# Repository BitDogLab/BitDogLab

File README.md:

<h1 align="center">BitDogLab V7</h1>

<p align="center">
  Open-source educational hardware for embedded systems, programming, electronics, and physical computing.
</p>

<p align="center">
  <a href="README.md">English</a> |
  <a href="README.pt-BR.md">Português</a>
</p>

<p align="center">
  
  <br>
  <a href="https://comunidade-bitdoglab.web.app">https://comunidade-bitdoglab.web.app</a>
</p>

<p align="center">
  Não é da área de tecnologia? Este repositório é o espaço técnico do projeto — para professores e demais usuários, a <a href="https://comunidade-bitdoglab.web.app"><strong>Comunidade BitDogLab</strong></a> é uma porta de entrada mais amigável, com documentação, códigos e aplicações prontas.
</p>

BitDogLab is an initiative of the **Escola 4.0 project at FEEC/Unicamp**. It brings together the Raspberry Pi Pico ecosystem and the main peripherals used in embedded systems, providing a practical platform for education, experimentation, and project development.

The current board is **BitDogLab Version 7**, with support for Raspberry Pi Pico-compatible modules based on the **RP2040** and **RP2350** microcontrollers.

Its hands-on approach supports the development of scientific thinking, problem solving, collaboration, and digital culture, competencies emphasized by Brazil's National Common Curricular Base (BNCC).

---

## Board and Peripherals

The board provides direct access to the main resources used in embedded-system education, including buttons, joystick, RGB LED, LED matrix, OLED display, microphone, buzzer, sensors, and expansion connectors.

---

## Recommended Learning Path

```mermaid
flowchart LR
    A[Start Here guide] --> B[Basic MicroPython examples]
    B --> C[Peripheral guides and libraries]
    C --> D[Applications and projects]
    D --> E[Hardware design and fabrication]
```

1. Follow the [Start Here guide](COMECE_POR_AQUI_BitDogLab_V7_MicroPython.md) to prepare the board and run the first test.
2. Study the [`basic-examples/`](basic-examples/) directory, organized from simpler to more advanced peripherals.
3. Use the [V7 peripheral guides](doc/Bitdoglab%20V7/) and reusable [`libs_software/`](libs_software/) modules.
4. Explore and develop applications in [`projects/`](projects/).
5. Study or manufacture the board using the public files in [`pcb-prototyping/`](pcb-prototyping/).

---

## Start Programming

The fastest text-based path is MicroPython with Thonny:

- [Illustrated MicroPython start guide](COMECE_POR_AQUI_BitDogLab_V7_MicroPython.md)
- [60 basic peripheral examples](basic-examples/README.md)
- [Complete peripheral test](testar_perifericos_gerais.py)
- [MicroPython firmware](firmware/)
- [Reusable software libraries](libs_software/README.md)

---

## Active Programming Projects

Below are the tools currently being developed within the BitDogLab ecosystem to support different entry points into programming — from block-based logic to AI-assisted code generation.

### 🧩 Blockly for BitDogLab

Blockly is the easiest way to get started with BitDogLab. It is designed for students and beginners learning programming logic and embedded systems. The tool runs directly in the browser without requiring installation.

To use it:

[Open Blockly for BitDogLab](https://bitdoglab-blocos.github.io/BIPES-BITDOGLAB/ui/)

1. Connect the BitDogLab to the computer using a USB cable.
2. Open Blockly for BitDogLab, preferably in Chrome or Edge.
3. Select the serial port corresponding to the board.
4. Drag and connect blocks to create the program.
5. Click `Run` or `Upload` to send the program to the BitDogLab.

> **Important:** If the board already contains a file named `main.py`, remove it before using Blockly. This file can prevent the tool from communicating correctly with the microcontroller.

<br>

### 📄 BIH — Hardware Information Database

<p align="center">
  
</p>

The **BIH** is a hardware information database designed to adapt the BitDogLab technical context for Large Language Models (LLMs), including ChatGPT, Gemini, and other AI assistants.

It describes the board's pin assignments, peripherals, interfaces, and hardware constraints. By providing the BIH to an LLM before requesting a program, the model can generate MicroPython or C/C++ code that better matches the BitDogLab hardware.

- [Open the BitDogLab V7 BIH](https://docs.google.com/document/d/13-68OqiU7ISE8U2KPRUXT2ISeBl3WPhXjGDFH52eWlU/edit?usp=sharing)
- [Open the visual hardware database](https://docs.google.com/document/d/1-2Eoo6H1gfTAlxZgFs26p7X4CeaLkS8X8hNTC96PetQ/edit?usp=sharing)

<br>

### 🔀 FluxCode

O BitDogLab FluxCode é um aplicativo Android que usa **IA multimodal** para transformar fluxogramas desenhados à mão em código **MicroPython** pronto para rodar na BitDogLab. A proposta é desplugada: o estudante primeiro desenvolve a lógica no papel usando símbolos de fluxograma, fotografa o desenho pelo app e recebe automaticamente o código correspondente, que pode ser executado ou salvo direto na placa.

Para usar:

[Baixar o BitDogLab FluxCode](https://drive.google.com/drive/folders/12xD7rVUsgQWKkneTLb5EA2QpiOx43nXb?usp=drive_link)

1. Conecte a BitDogLab ao smartphone via USB.
2. Desenhe o fluxograma em papel usando o gabarito de símbolos.
3. No app, toque em **Foto Código** e fotografe o fluxograma.
4. Revise o código MicroPython e o pseudocódigo gerados automaticamente.
5. Toque em **Executar** para rodar na placa, ou salve como `main.py` para execução automática ao ligar.

> Disponível apenas para Android. Requer MicroPython instalado na placa e um cabo USB compatível com transferência de dados (não apenas carregamento).

<br>

### 🎨 Pixel Art Application

**UNDER CONSTRUCTION**

---

## BitDogLab V7 Hardware

BitDogLab V7 integrates an RGB LED, a 5x5 WS2812B matrix, three buttons, analog joystick, buzzer, analog microphone, OLED display, power monitoring, and expansion connections around a Raspberry Pi Pico-compatible module.

The V7 hardware was developed in **Altium Designer**. Source files, schematic, PCB layout, BOM, pick-and-place data, STEP model, and public Gerber files for fabrication are available in [`pcb-prototyping/BitDogLab V7/`](pcb-prototyping/BitDogLab%20V7/).

BitDogLab V6 was developed in **KiCad** and remains available for study and fabrication. See the complete [PCB and fabrication documentation](pcb-prototyping/README.md).

---

## Repository Structure

| Path | Content |
|---|---|
| [`basic-examples/`](basic-examples/) | Beginner-friendly MicroPython examples organized by peripheral. |
| [`doc/`](doc/) | BitDogLab V6 and V7 documentation and peripheral guides. |
| [`firmware/`](firmware/) | MicroPython firmware and installation resources. |
| [`libs_software/`](libs_software/) | Reusable MicroPython drivers and helper modules. |
| [`pcb-prototyping/`](pcb-prototyping/) | PCB source files and public manufacturing files. |
| [`projects/`](projects/) | Applications, sensors, IoT, tools, and hardware expansions. |

---

## Open Hardware and License

BitDogLab is open hardware. Its design and fabrication files are publicly available for study, modification, and manufacturing.

The project is licensed under the **CERN Open Hardware Licence Version 2 - Strongly Reciprocal (CERN-OHL-S v2.0)**. See [`LICENSE`](LICENSE).

---

## Initiative and Contributors

- Initiative: **Escola 4.0 - FEEC/Unicamp**
- Project coordination: **Prof. Dr. Fabiano Fruett**
- Contributors: students and collaborators from Escola 4.0 and FEEC/Unicamp
- Support: IEEE-EDS STEM outreach program and CNPq - INCT Namitec

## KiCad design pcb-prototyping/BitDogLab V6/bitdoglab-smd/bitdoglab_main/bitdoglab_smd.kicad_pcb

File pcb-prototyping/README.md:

# PCB Prototyping / Prototipagem de PCB

[English](#english) | [Portugues](#portugues)

## English

This directory contains the public PCB design and fabrication files for the BitDogLab boards.

The folder name is `pcb-prototyping` because not every file here was created in KiCad. It includes KiCad projects, Altium projects, manufacturing outputs, 3D models, images, BOM files and support libraries.

### Folder Structure

```text
pcb-prototyping/
+-- BitDogLab V6/
|   +-- bitdoglab-through-hole/
|   +-- bitdoglab-smd/
|   +-- component-libraries/
+-- BitDogLab V7/
    +-- Project Outputs for BitDogLab V7/
    +-- __Previews/
    +-- History/
    +-- bitdoglab-v7-pcb-top-view.png
    +-- bitdoglab-v7-pcb-bottom-view.png
```

### BitDogLab V6

BitDogLab V6 was developed in KiCad.

- `bitdoglab-through-hole/`: through-hole/DIY KiCad project files.
- `bitdoglab-smd/`: SMD KiCad project files, schematic, PCB layout, fabrication outputs and board images.
- `component-libraries/`: symbols, footprints, 3D models and support files used by the KiCad projects.

Common KiCad files found here:

- `.kicad_pro`: KiCad project file.
- `.kicad_sch`: schematic file.
- `.kicad_pcb`: PCB layout file.
- `.kicad_mod`: footprint file.
- `.kicad_sym`: symbol library file.
- `.step` / `.stp`: 3D model files.
- `.zip`: fabrication package when available.
- `.csv` / `.xlsx`: BOM or component data when available.

### BitDogLab V7

BitDogLab V7 was developed in Altium Designer.

Main files:

- `BitDogLab V7.PrjPcb`: Altium PCB project.
- `BitDogLab V7.SchDoc`: Altium schematic document.
- `BitDogLab V7.PcbDoc`: Altium PCB layout document.
- `BitDogLab V7.OutJob`: Altium output job configuration.
- `BitDogLab V7.pdf`: exported schematic/documentation PDF.
- `BitDogLab V7_Lista de Materiais com Custo.xlsx`: bill of materials with cost information.
- `BitDogLab V7_Gerber.rar`: Gerber fabrication package.
- `Project Outputs for BitDogLab V7/`: manufacturing outputs exported from the project, including Gerber layers, drill reports, BOM, pick-and-place and 3D STEP model.
- `bitdoglab-v7-pcb-top-view.png`: technical top view image of the PCB.
- `bitdoglab-v7-pcb-bottom-view.png`: technical bottom view image of the PCB.

### Public Fabrication Files

Gerber files are publicly available for fabrication. They can be used by PCB manufacturers to produce the board.

Before ordering a board, review the fabrication package, BOM, drill files and pick-and-place data. Manufacturing settings can vary by supplier, so the files should always be checked in a Gerber viewer or CAM tool before production.

### Notes

- KiCad is recommended for opening and editing the BitDogLab V6 project files.
- Altium Designer is recommended for opening and editing the BitDogLab V7 source project files.
- Gerber and drill files can usually be inspected with vendor tools or independent Gerber viewers.
- Board images are provided as visual references and are not a replacement for fabrication data.

## Portugues

Esta pasta contem os arquivos publicos de projeto e fabricacao das placas BitDogLab.

O nome da pasta e `pcb-prototyping` porque nem todo arquivo aqui foi desenvolvido no KiCad. Ela inclui projetos KiCad, projetos Altium, arquivos de fabricacao, modelos 3D, imagens, listas de materiais e bibliotecas de apoio.

### Estrutura de Pastas

```text
pcb-prototyping/
+-- BitDogLab V6/
|   +-- bitdoglab-through-hole/
|   +-- bitdoglab-smd/
|   +-- component-libraries/
+-- BitDogLab V7/
    +-- Project Outputs for BitDogLab V7/
    +-- __Previews/
    +-- History/
    +-- bitdoglab-v7-pcb-top-view.png
    +-- bitdoglab-v7-pcb-bottom-view.png
```

### BitDogLab V6

A BitDogLab V6 foi desenvolvida no KiCad.

- `bitdoglab-through-hole/`: arquivos KiCad da versao through-hole/DIY.
- `bitdoglab-smd/`: arquivos KiCad da versao SMD, esquematico, layout da placa, saidas de fabricacao e imagens da placa.
- `component-libraries/`: simbolos, footprints, modelos 3D e arquivos de apoio usados pelos projetos KiCad.

Arquivos KiCad comuns nesta pasta:

- `.kicad_pro`: arquivo de projeto KiCad.
- `.kicad_sch`: arquivo de esquematico.
- `.kicad_pcb`: arquivo de layout da PCB.
- `.kicad_mod`: arquivo de footprint.
- `.kicad_sym`: biblioteca de simbolos.
- `.step` / `.stp`: modelos 3D.
- `.zip`: pacote de fabricacao quando disponivel.
- `.csv` / `.xlsx`: BOM ou dados de componentes quando disponiveis.

### BitDogLab V7

A BitDogLab V7 foi desenvolvida no Altium Designer.

Arquivos principais:

- `BitDogLab V7.PrjPcb`: projeto PCB do Altium.
- `BitDogLab V7.SchDoc`: documento de esquematico do Altium.
- `BitDogLab V7.PcbDoc`: documento de layout da PCB no Altium.
- `BitDogLab V7.OutJob`: configuracao de saidas do Altium.
- `BitDogLab V7.pdf`: PDF exportado com esquematico/documentacao.
- `BitDogLab V7_Lista de Materiais com Custo.xlsx`: lista de materiais com informacoes de custo.
- `BitDogLab V7_Gerber.rar`: pacote Gerber para fabricacao.
- `Project Outputs for BitDogLab V7/`: saidas de fabricacao exportadas do projeto, incluindo camadas Gerber, relatorios de furo, BOM, pick-and-place e modelo 3D STEP.
- `bitdoglab-v7-pcb-top-view.png`: imagem tecnica da face superior da PCB.
- `bitdoglab-v7-pcb-bottom-view.png`: imagem tecnica da face inferior da PCB.

### Arquivos Publicos para Fabricacao

Os arquivos Gerber estao disponiveis publicamente para fabricacao. Eles podem ser usados por fabricantes de PCB para produzir a placa.

Antes de encomendar uma placa, revise o pacote de fabricacao, a BOM, os arquivos de furo e os dados de pick-and-place. As configuracoes de fabricacao podem variar conforme o fornecedor, entao os arquivos devem sempre ser conferidos em um visualizador Gerber ou ferramenta CAM antes da producao.

### Observacoes

- O KiCad e recomendado para abrir e editar os arquivos da BitDogLab V6.
- O Altium Designer e recomendado para abrir e editar os arquivos fonte da BitDogLab V7.
- Arquivos Gerber e de furo normalmente podem ser inspecionados em ferramentas dos fabricantes ou em visualizadores Gerber independentes.
- As imagens da placa servem como referencia visual e nao substituem os arquivos de fabricacao.

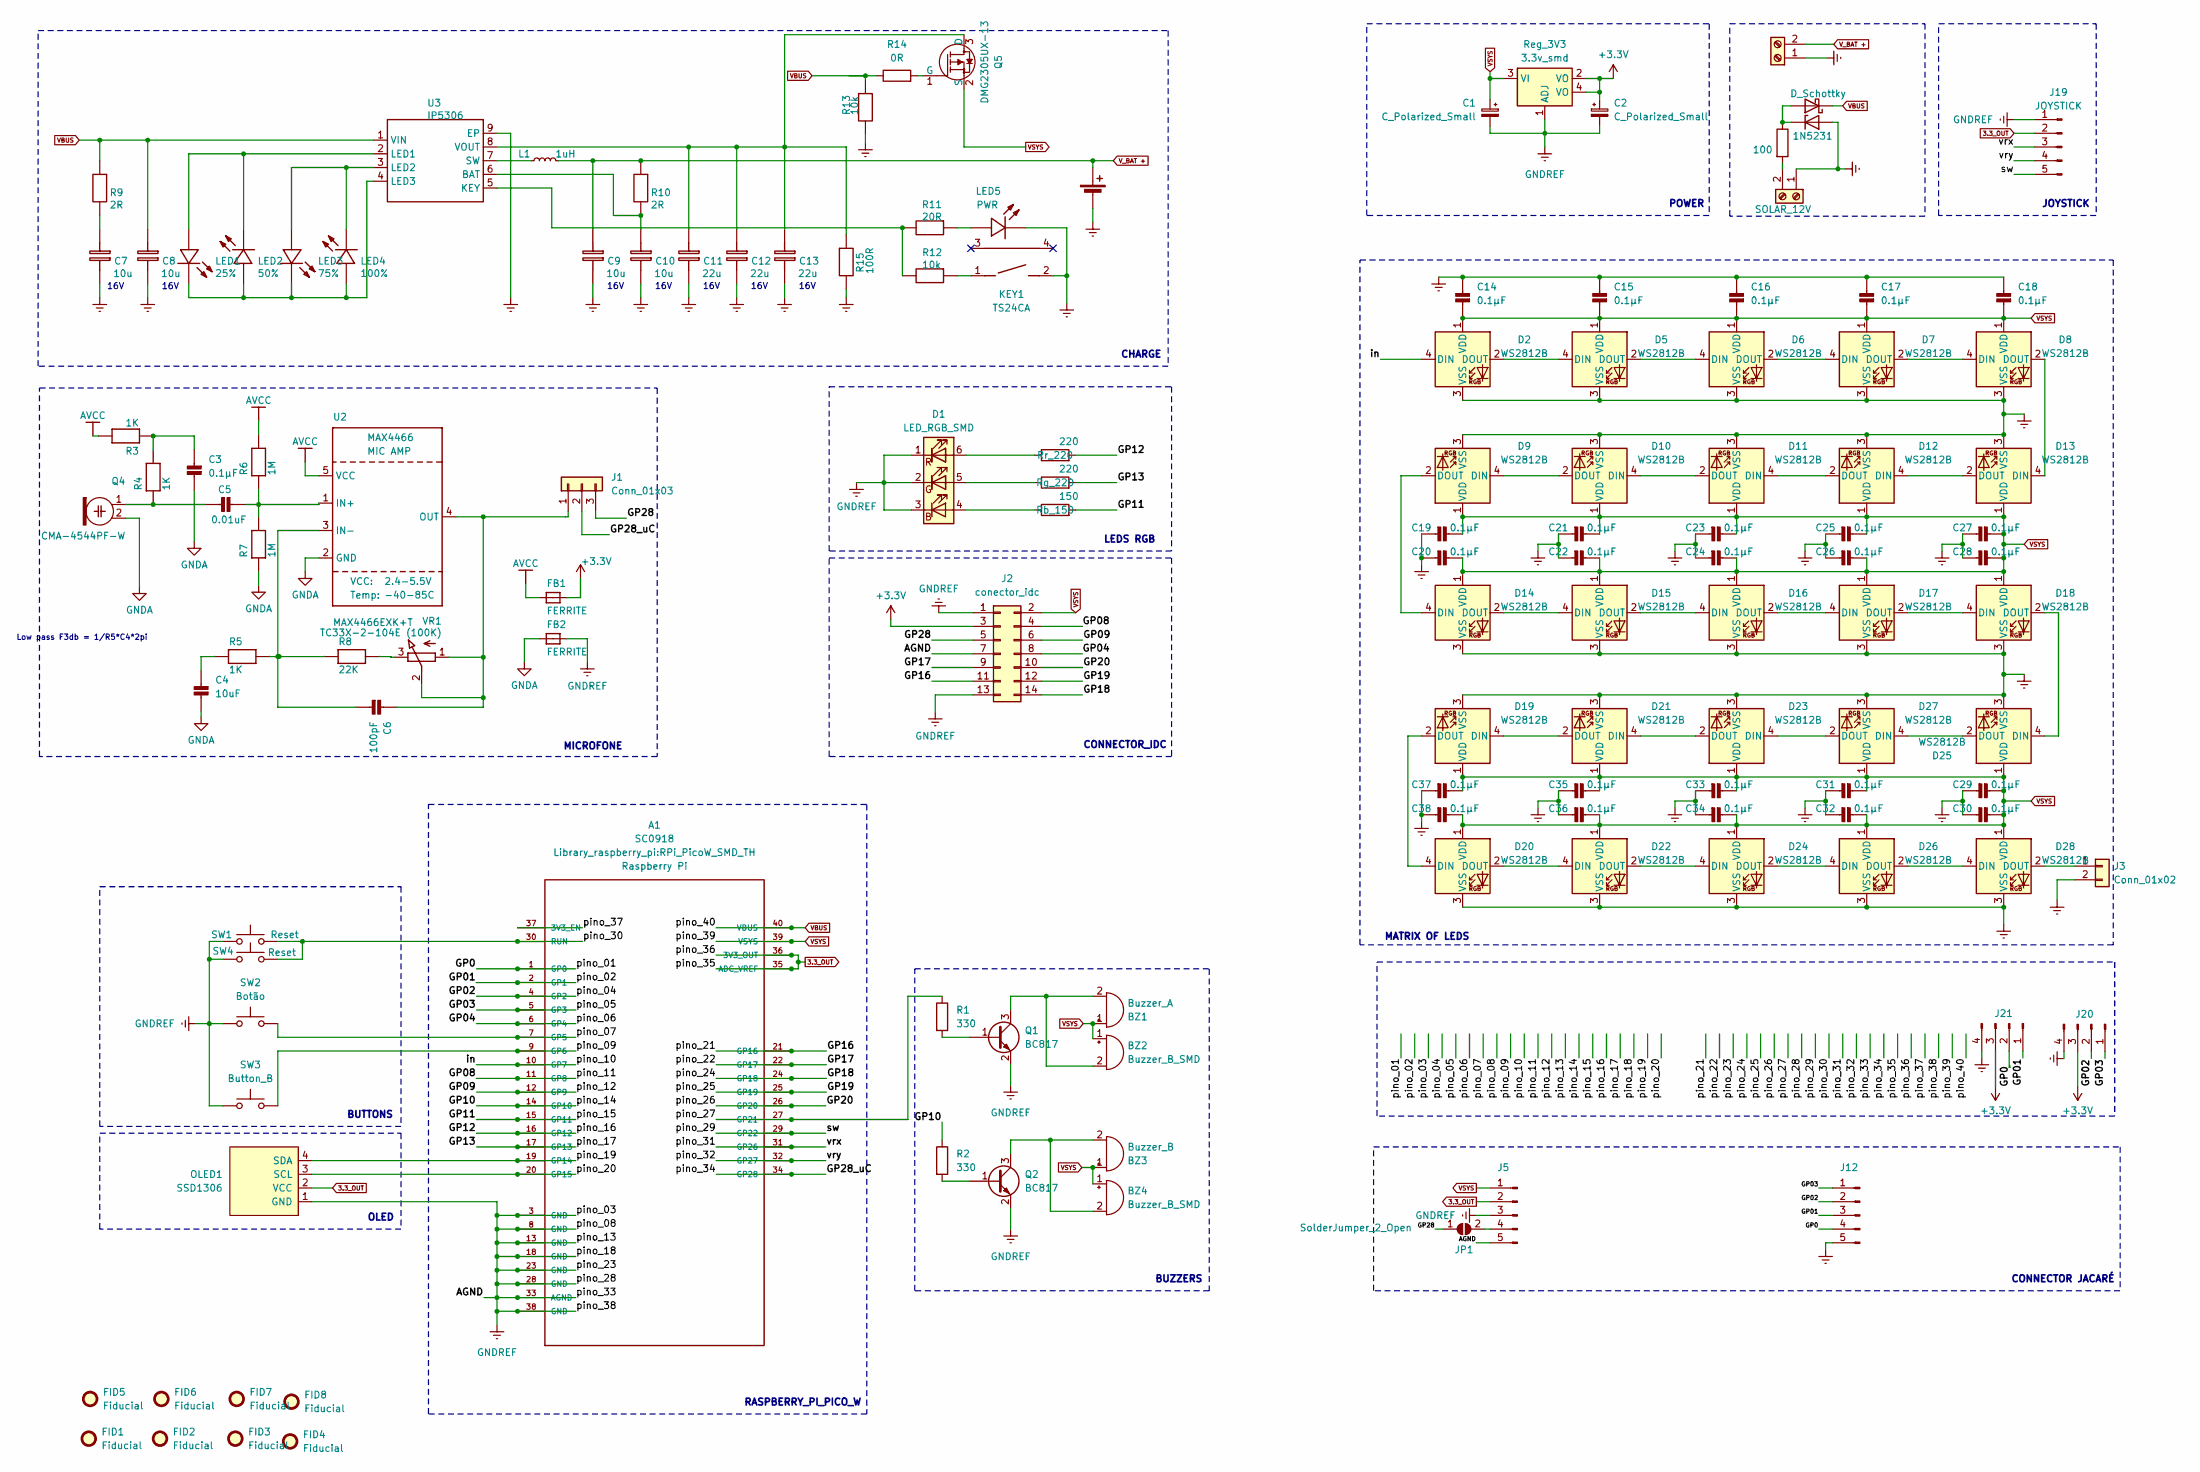
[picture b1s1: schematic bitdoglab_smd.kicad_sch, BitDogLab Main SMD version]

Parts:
A1: SC0918; RPi_PicoW_SMD_TH; PARTREV 1.6
BT1: Battery_Cell; BatteryHolder_MPD_BH-18650-PC2
BZ1: Buzzer_A; Buzzer_12x9.5RM7.6
BZ2, BZ4: Buzzer_B_SMD; MagneticBuzzer_CUI_CMT-8504-100-SMT
BZ3: Buzzer_B; Buzzer_12x9.5RM7.6
C1, C2: C_Polarized_Small; CP_Elec_5x5.9
C3, C14, C15, C16, C17, C18, C19, C20, C21, C22, C23, C24, C25, C26, C27, C28, C29, C30, C31, C32, C33, C34, C35, C36, C37, C38: 0.1µF; C_0402_1005Metric
C4: 10uF; C_0805_2012Metric
C5: 0.01uF; C_0402_1005Metric
C6: 100pF; C_0402_1005Metric
C7, C8, C9, C10: 10u; R_0805_2012Metric; MANUFACTURER PART CL21A106KAYNNNE
C11, C12, C13: 22u; R_0805_2012Metric; MANUFACTURER PART CL21A226MAQNNNE
CARGA_SOLAR1: SOLAR_12V; JST_EH_B2B-EH-A_1x02_P2.50mm_Vertical
D1: LED_RGB_SMD; LED_RGB_5050-6
D2, D5, D6, D7, D8, D9, D10, D11, D12, D13, D14, D15, D16, D17, D18, D19, D20, D21, D22, D23, D24, D25, D26, D27, D28: WS2812B; LED_WS2812B_PLCC4_5.0x5.0mm_P3.2mm
D3: 1N5231; D_T-1_P5.08mm_Horizontal
D4: D_Schottky; D_SOD-123
FB1, FB2: FERRITE; L_0603_1608Metric
FID1, FID2, FID3, FID4, FID5, FID6, FID7, FID8: Fiducial; Fiducial_1mm_Mask2mm
J1: Conn_01x03; PinHeader_1x03_P2.54mm_Vertical
J2: conector_idc; PinHeader_2x07_P2.54mm_Vertical
J3: Conn_01x02; PinHeader_1x02_P2.54mm_Vertical
J5, J12: Conn_01x05_Pin; PinHeader_1x05_P2.54mm_Vertical
J19: JOYSTICK; ky-023
J20, J21: Conn_01x04_Pin; JST_EH_B4B-EH-A_1x04_P2.50mm_Vertical
JP1: SolderJumper_2_Open; SolderJumper-2_P1.3mm_Open_TrianglePad1.0x1.5mm
KEY1: TS24CA; SW_SPST_CK_KMS2xxGP; MANUFACTURER PART TS24CA
L1: 1uH; L_Bourns_SRP7028A_7.3x6.6mm
LED1: 25%; LED_0805_2012Metric; MANUFACTURER PART FC-2012HRK-620D
LED2: 50%; LED_0805_2012Metric; MANUFACTURER PART 17-21SUYC/TR8
LED3: 75%; LED_0805_2012Metric; MANUFACTURER PART 17-21SUYC/TR8
LED4: 100%; LED_0805_2012Metric; MANUFACTURER PART 0805G (Green)
LED5: PWR; LED_0805_2012Metric; MANUFACTURER PART ORH-B35A
OLED1: SSD1306; 128x64OLED
Q1, Q2: BC817; SOT-23
Q4: CMA-4544PF-W; Buzzer_12x9.5RM7.6
Q5: DMG2305UX-13; SOT-23-3; MPN DMG2305UX-13; Digi-Key_PN DMG2305UX-13DICT-ND
R1, R2: 330; R_0603_1608Metric
R3, R4, R5: 1K; R_0603_1608Metric
R6, R7: 1M; R_0603_1608Metric
R8: 22K; R_0603_1608Metric
R9, R10: 2R; R_0603_1608Metric; MANUFACTURER PART RS-05L2R00FT
R11: 20R; R_0603_1608Metric; MANUFACTURER PART 0805W8F200JT5E
R12, R13: 10k; R_0603_1608Metric; MANUFACTURER PART 0805W8F1002T5E
R14: 0R; R_0603_1608Metric
R15: 100R; R_1210_3225Metric; MANUFACTURER PART RC1210FR-07100RL
R_1W1: 100; R_0603_1608Metric
Rb_150: 150; R_0603_1608Metric
Reg_3V3: 3.3v_smd; SOT-223
Rg_220: 220; R_0603_1608Metric
Rr_220: 220; R_0603_1608Metric
SW1: Reset; SW_PUSH_6mm
SW2: Botão; SW_PUSH_6mm_b
SW3: Button_B; SW_PUSH_6mm_b
SW4: Reset; SW_Push_1P1T_NO_6x6mm_H9.5mm
U2: MAX4466EXK+T; SOT-353_SC-70-5
U3: IP5306; SOP-8_5.28x5.23mm_P1.27mm; MANUFACTURER PART IP5306_4.35V
VR1: TC33X-2-104E (100K); Potentiometer_Bourns_TC33X_Vertical
V_BAT1: V_BAT; JST_EH_B2B-EH-A_1x02_P2.50mm_Vertical

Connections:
3.3_OUT: A1.35 (ADC_VREF), A1.36 (3V3_OUT), J5.2, J19.2, OLED1.2 (VCC)
+3.3V: C2.1, FB1.2, J2.3, J20.3, J21.3, Reg_3V3.2 (VO), Reg_3V3.4 (VO)
/GP0: A1.1 (GP0), J12.4, J21.2
/GP01: A1.2 (GP1), J12.3, J21.1
/GP02: A1.4 (GP2), J12.2, J20.2
/GP03: A1.5 (GP3), J12.1, J20.1
/GP04: A1.6 (GP4), J2.8
/GP08: A1.11 (GP8), J2.4
/GP09: A1.12 (GP9), J2.6
/GP10: A1.14 (GP10), R2.1
/GP11: A1.15 (GP11), Rb_150.2
/GP12: A1.16 (GP12), Rr_220.2
/GP13: A1.17 (GP13), Rg_220.2
/GP16: A1.21 (GP16), J2.11
/GP17: A1.22 (GP17), J2.9
/GP18: A1.24 (GP18), J2.14
/GP19: A1.25 (GP19), J2.12
/GP20: A1.26 (GP20), J2.10
/GP28: J1.3, J2.5, JP1.1 (A)
/GP28_uC: A1.34 (GP28), J1.2
/in: A1.10 (GP7), D2.4 (DIN)
/pino_07: A1.7 (GP5), SW2.1
/pino_09: A1.9 (GP6), SW3.1
/pino_19: A1.19 (GP14), OLED1.4 (SDA)
/pino_20: A1.20 (GP15), OLED1.3 (SCL)
/pino_27: A1.27 (GP21), R1.1
/pino_29: A1.29 (GP22), J19.5
/pino_30: A1.30 (RUN), SW1.1, SW4.1
/pino_31: A1.31 (GP26), J19.3
/pino_32: A1.32 (GP27), J19.4
/pino_37: A1.37 (3V3_EN)
AVCC: FB1.1, R3.2, R6.2, U2.5 (VCC)
GNDA: C3.2, C4.2, FB2.1, Q4.2 (+), R7.1, U2.2 (GND)
GNDREF: A1.3 (GND), A1.8 (GND), A1.13 (GND), A1.18 (GND), A1.23 (GND), A1.28 (GND), A1.33 (AGND), A1.38 (GND), BT1.2 (-), C1.2, C2.2, C7.2, C8.2, C9.2, C10.2, C11.2, C12.2, C13.2, C14.1, C15.1, C16.1, C17.1, C18.1, C19.1, C20.1, C21.1, C22.1, C23.1, C24.1, C25.1, C26.1, C27.1, C28.1, C29.1, C30.1, C31.1, C32.1, C33.1, C34.1, C35.1, C36.1, C37.1, C38.1, CARGA_SOLAR1.1, D1.1 (RK), D1.2 (GK), D1.3 (BK), D2.3 (VSS), D3.2 (A), D5.3 (VSS), D6.3 (VSS), D7.3 (VSS), D8.3 (VSS), D9.3 (VSS), D10.3 (VSS), D11.3 (VSS), D12.3 (VSS), D13.3 (VSS), D14.3 (VSS), D15.3 (VSS), D16.3 (VSS), D17.3 (VSS), D18.3 (VSS), D19.3 (VSS), D20.3 (VSS), D21.3 (VSS), D22.3 (VSS), D23.3 (VSS), D24.3 (VSS), D25.3 (VSS), D26.3 (VSS), D27.3 (VSS), D28.3 (VSS), FB2.2, J2.1, J2.7, J2.13, J3.2, J5.3, J5.5, J12.5, J19.1, J20.4, J21.4, KEY1.2, LED5.2 (K), OLED1.1 (GND), Q1.2 (E), Q2.2 (E), R13.2, R15.2, Reg_3V3.1 (ADJ), SW1.2, SW2.2, SW3.2, SW4.2, U3.9 (EP), V_BAT1.1
unnamed: BZ1.2 (+), BZ2.2 (+), Q1.3 (C)
unnamed: BZ3.2 (+), BZ4.2 (+), Q2.3 (C)
unnamed: C3.1, R3.1, R4.2
unnamed: C4.1, R5.1
unnamed: C5.1, Q4.1 (-), R4.1
unnamed: C5.2, R6.1, R7.2, U2.1 (IN+)
unnamed: C6.1, J1.1, U2.4 (OUT), VR1.1 (A), VR1.2 (S)
unnamed: C6.2, R5.2, R8.1, U2.3 (IN-)
unnamed: C7.1, R9.1
unnamed: CARGA_SOLAR1.2, R_1W1.2
unnamed: D1.4 (BA), Rb_150.1
unnamed: D1.5 (GA), Rg_220.1
unnamed: D1.6 (RA), Rr_220.1
unnamed: D2.2 (DOUT), D5.4 (DIN)
unnamed: D3.1 (K), D4.2 (A), R_1W1.1
unnamed: D5.2 (DOUT), D6.4 (DIN)
unnamed: D6.2 (DOUT), D7.4 (DIN)
unnamed: D7.2 (DOUT), D8.4 (DIN)
unnamed: D10.4 (DIN), D11.2 (DOUT)
unnamed: D9.4 (DIN), D10.2 (DOUT)
unnamed: D11.4 (DIN), D12.2 (DOUT)
unnamed: D12.4 (DIN), D13.2 (DOUT)
unnamed: D8.2 (DOUT), D13.4 (DIN)
unnamed: D9.2 (DOUT), D14.4 (DIN)
unnamed: D14.2 (DOUT), D15.4 (DIN)
unnamed: D15.2 (DOUT), D16.4 (DIN)
unnamed: D16.2 (DOUT), D17.4 (DIN)
unnamed: D17.2 (DOUT), D18.4 (DIN)
unnamed: D18.2 (DOUT), D25.4 (DIN)
unnamed: D19.4 (DIN), D21.2 (DOUT)
unnamed: D19.2 (DOUT), D20.4 (DIN)
unnamed: D20.2 (DOUT), D22.4 (DIN)
unnamed: D21.4 (DIN), D23.2 (DOUT)
unnamed: D22.2 (DOUT), D24.4 (DIN)
unnamed: D23.4 (DIN), D27.2 (DOUT)
unnamed: D24.2 (DOUT), D26.4 (DIN)
unnamed: D25.2 (DOUT), D27.4 (DIN)
unnamed: D26.2 (DOUT), D28.4 (DIN)
unnamed: D28.2 (DOUT), J3.1
unnamed: J5.4, JP1.2 (B)
unnamed: KEY1.1, R12.1
unnamed: LED1.1 (A), LED2.2 (K), U3.2 (LED1)
unnamed: LED1.2 (K), LED2.1 (A), LED3.2 (K), LED4.1 (A), U3.4 (LED3)
unnamed: LED3.1 (A), LED4.2 (K), U3.3 (LED2)
unnamed: LED5.1 (A), R11.1
unnamed: Q1.1 (B), R1.2
unnamed: Q2.1 (B), R2.2
unnamed: C11.1, C12.1, C13.1, Q5.3 (D), R15.1, U3.8 (VOUT)
unnamed: Q5.1 (G), R14.2
unnamed: C10.1, R10.1, U3.6 (BAT)
unnamed: R11.2, R12.2, U3.5 (KEY)
unnamed: L1.1, U3.7 (SW)
unnamed: R8.2, VR1.3 (E)
VBUS: A1.40 (VBUS), C8.1, D4.1 (K), R9.2, R13.1, R14.1, U3.1 (VIN)
VSYS: A1.39 (VSYS), BZ1.1 (-), BZ2.1 (-), BZ3.1 (-), BZ4.1 (-), C1.1, C14.2, C15.2, C16.2, C17.2, C18.2, C19.2, C20.2, C21.2, C22.2, C23.2, C24.2, C25.2, C26.2, C27.2, C28.2, C29.2, C30.2, C31.2, C32.2, C33.2, C34.2, C35.2, C36.2, C37.2, C38.2, D2.1 (VDD), D5.1 (VDD), D6.1 (VDD), D7.1 (VDD), D8.1 (VDD), D9.1 (VDD), D10.1 (VDD), D11.1 (VDD), D12.1 (VDD), D13.1 (VDD), D14.1 (VDD), D15.1 (VDD), D16.1 (VDD), D17.1 (VDD), D18.1 (VDD), D19.1 (VDD), D20.1 (VDD), D21.1 (VDD), D22.1 (VDD), D23.1 (VDD), D24.1 (VDD), D25.1 (VDD), D26.1 (VDD), D27.1 (VDD), D28.1 (VDD), J2.2, J5.1, Q5.2 (S), Reg_3V3.3 (VI)
V_BAT +: BT1.1 (+), C9.1, L1.2, R10.2, V_BAT1.2

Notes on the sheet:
POWER
OLED
BUZZERS
LEDS RGB
BUTTONS
16V
CONNECTOR_IDC
CONNECTOR JACARÉ
Low pass F3db = 1/R5*C4*2pi
CHARGE
MICROFONE
MATRIX OF LEDS
RASPBERRY_PI_PICO_W
JOYSTICK

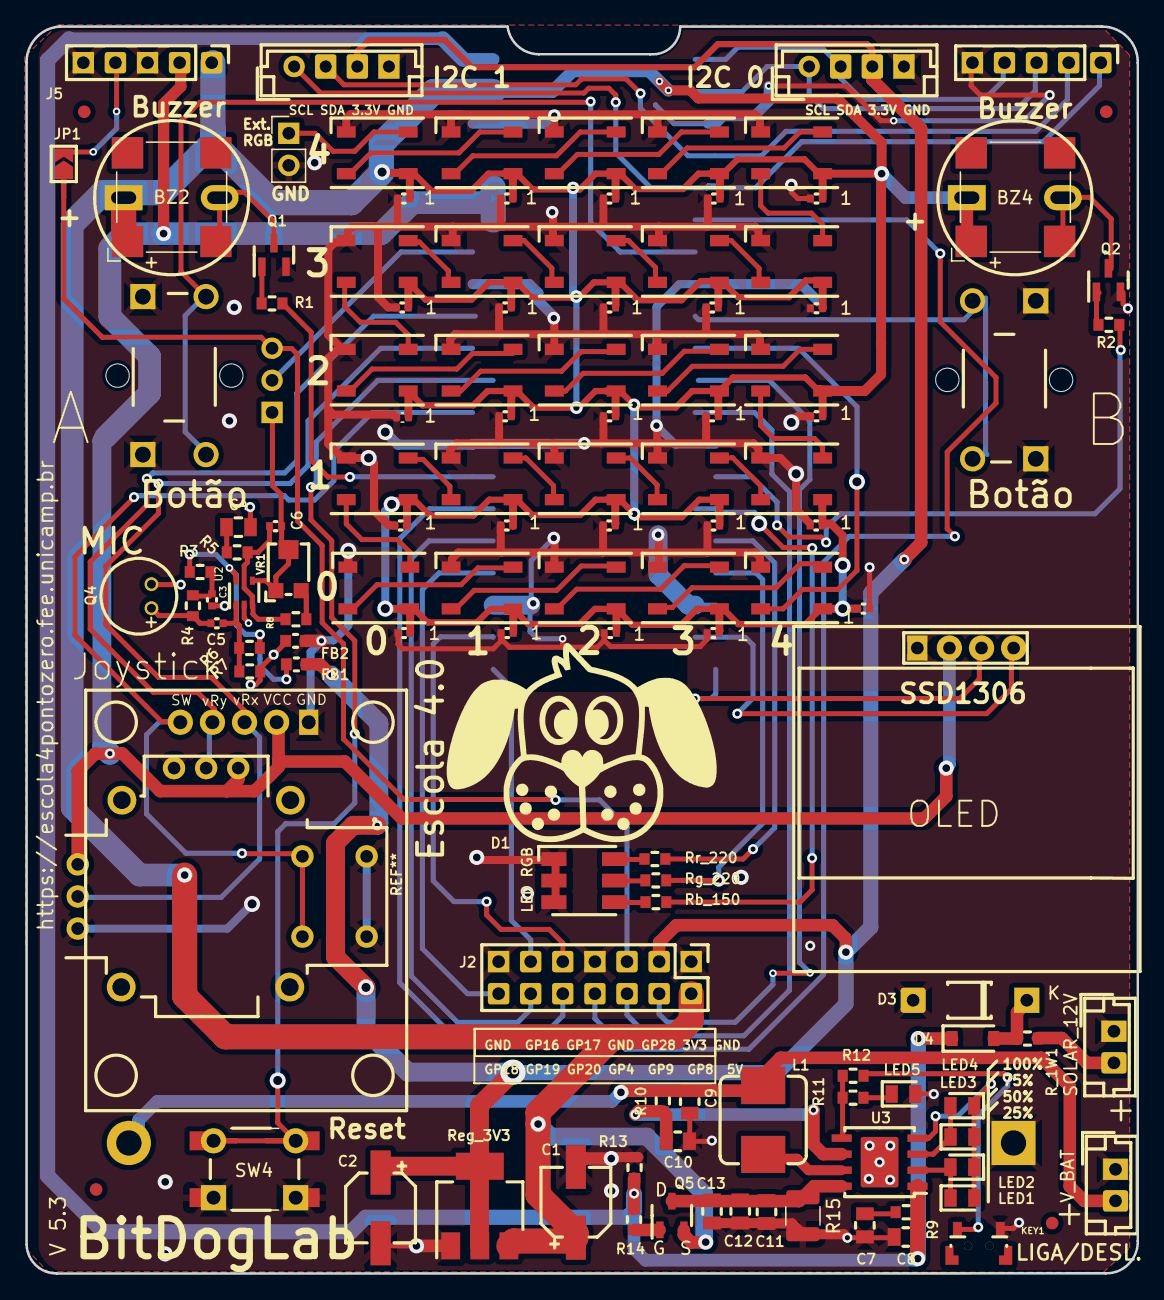
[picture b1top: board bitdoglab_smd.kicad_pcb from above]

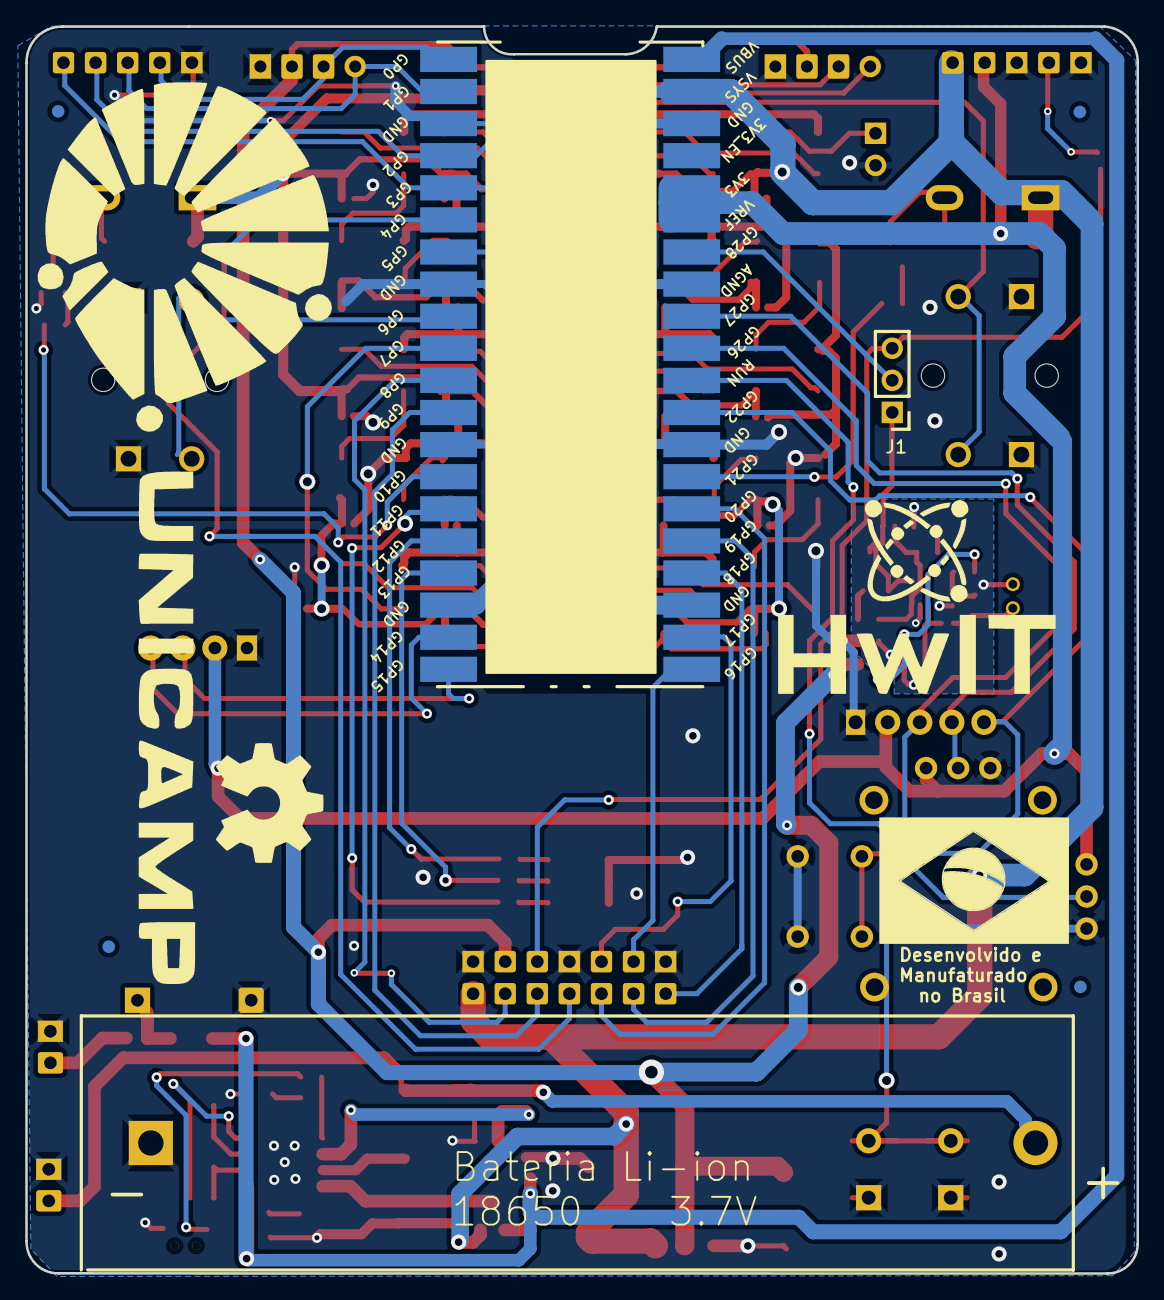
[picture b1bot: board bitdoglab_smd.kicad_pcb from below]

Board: 2 copper layers, 87.9 x 98.7 mm, 137 parts (11 on the bottom side), 89 nets.

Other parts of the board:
.: LOGO; Brasil_4
.#2: LOGO; 1Logo
.#3: LOGO; unicamp V2A
G1: LOGO; logo bitDog 25mm
G3: LOGO

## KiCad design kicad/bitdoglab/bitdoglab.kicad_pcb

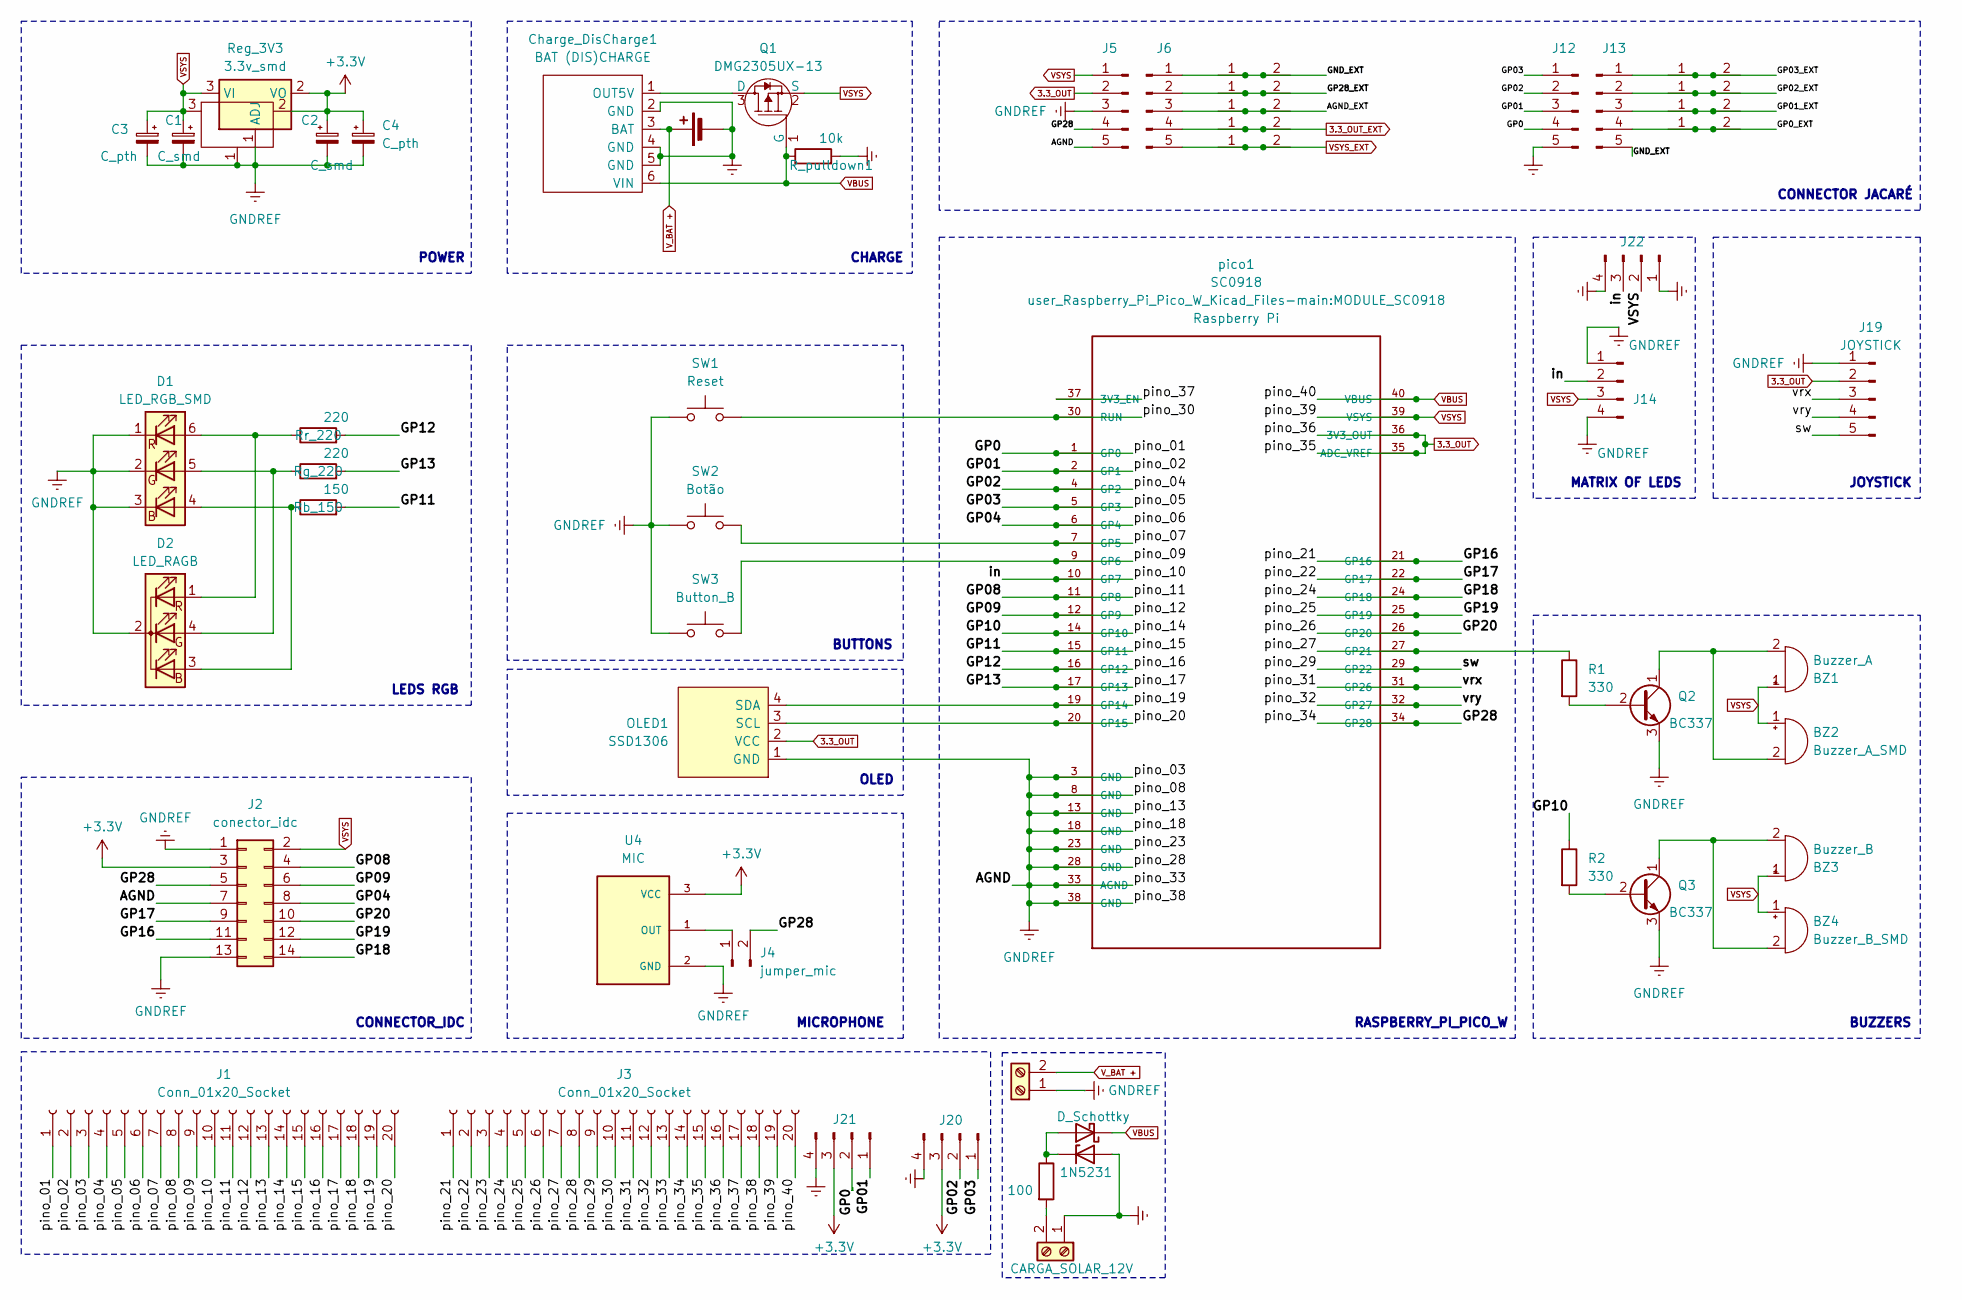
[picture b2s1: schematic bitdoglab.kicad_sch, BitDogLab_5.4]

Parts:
BT1: Battery_Cell; BatteryHolder_MPD_BH-18650-PC2
BZ1: Buzzer_A; Buzzer_12x9.5RM7.6
BZ2: Buzzer_A_SMD; MagneticBuzzer_CUI_CMT-8504-100-SMT
BZ3: Buzzer_B; Buzzer_12x9.5RM7.6
BZ4: Buzzer_B_SMD; MagneticBuzzer_CUI_CMT-8504-100-SMT
C1, C2: C_smd; CP_Elec_5x5.9
C3, C4: C_pth; CP_Radial_D5.0mm_P2.50mm
CARGA_SOLAR1: CARGA_SOLAR_12V; JST_EH_B2B-EH-A_1x02_P2.50mm_Vertical
Charge_DisCharge1: BAT (DIS)CHARGE; Charger2A
D1: LED_RGB_SMD; LED_RGB_5050-6
D2: LED_RAGB; LED_D5.0mm-4_RGB_Wide_Pins
D3: 1N5231; D_T-1_P5.08mm_Horizontal
D4: D_Schottky; D_DO-15_P3.81mm_Vertical_KathodeUp
J1, J3: Conn_01x20_Socket; PinHeader_1x20_P2.54mm_Vertical
J2: conector_idc; PinHeader_2x07_P2.54mm_Vertical
J4: jumper_mic; PinHeader_1x02_P2.54mm_Vertical
J5, J6, J12, J13: Conn_01x05_Pin; PinHeader_1x05_P2.54mm_Vertical
J7, J9: GND; SolderWire-2sqmm_1x02_P7.8mm_D2mm_OD3.9mm
J8: ANA-IN; SolderWire-2sqmm_1x02_P7.8mm_D2mm_OD3.9mm
J10: 3V3; SolderWire-2sqmm_1x02_P7.8mm_D2mm_OD3.9mm
J11: 5V-VSYS; SolderWire-2sqmm_1x02_P7.8mm_D2mm_OD3.9mm
J14: 5x5 Matrix led; Ws2812_led_5050_rgb_5x5
J15: 0; SolderWire-2sqmm_1x02_P7.8mm_D2mm_OD3.9mm
J16: 1; SolderWire-2sqmm_1x02_P7.8mm_D2mm_OD3.9mm
J17: 2; SolderWire-2sqmm_1x02_P7.8mm_D2mm_OD3.9mm
J18: 3; SolderWire-2sqmm_1x02_P7.8mm_D2mm_OD3.9mm
J19: JOYSTICK; ky-023
J20, J21, J22: Conn_01x04_Pin; JST_EH_B4B-EH-A_1x04_P2.50mm_Vertical
OLED1: SSD1306; 128x64OLED
Q1: DMG2305UX-13; SOT-23-3; MPN DMG2305UX-13; Digi-Key_PN DMG2305UX-13DICT-ND
Q2, Q3: BC337; TO-92
R1, R2: 330; R_Axial_DIN0207_L6.3mm_D2.5mm_P7.62mm_Horizontal
R_1W1: 100; R_Axial_DIN0411_L9.9mm_D3.6mm_P12.70mm_Horizontal
R_pulldown1: 10k; R_Axial_DIN0207_L6.3mm_D2.5mm_P7.62mm_Horizontal
Rb_150: 150; R_Axial_DIN0207_L6.3mm_D2.5mm_P7.62mm_Horizontal
Reg_3V3: 3.3v_smd; SOT-223
Rg_220: 220; R_Axial_DIN0207_L6.3mm_D2.5mm_P7.62mm_Horizontal
Rr_220: 220; R_Axial_DIN0207_L6.3mm_D2.5mm_P7.62mm_Horizontal
SW1: Reset; SW_PUSH_6mm
SW2: Botão; SW_PUSH_6mm
SW3: Button_B; SW_PUSH_6mm
U1: 3.3v_tht; TO-220-3_Vertical; MPN LD1117V33
U4: MIC; MODULE_1063; PARTREV 1.0
V_BAT1: V_BAT; JST_EH_B2B-EH-A_1x02_P2.50mm_Vertical
pico1: SC0918; MODULE_SC0918; PARTREV 1.6

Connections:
3.3_OUT: J3.15, J3.16, J5.2, J19.2, OLED1.2 (VCC), pico1.35 (ADC_VREF), pico1.36 (3V3_OUT); also elsewhere on the board
3.3_OUT_EXT: J6.4, J10.1, J10.2
+3.3V: C2.1, C4.1, J2.3, J20.3, J21.3, Reg_3V3.2 (VO), U1.2, U4.3 (VCC)
/AGND_EXT: J6.3, J9.1, J9.2
/GND_EXT: J6.1, J7.1, J7.2, J13.5
/GP0: J1.1, J12.4, J21.2, pico1.1 (GP0)
/GP0_EXT: J13.4, J18.1, J18.2
/GP01: J1.2, J12.3, J21.1, pico1.2 (GP1)
/GP01_EXT: J13.3, J17.1, J17.2
/GP02: J1.4, J12.2, J20.2, pico1.4 (GP2)
/GP02_EXT: J13.2, J16.1, J16.2
/GP03: J1.5, J12.1, J20.1, pico1.5 (GP3)
/GP03_EXT: J13.1, J15.1, J15.2
/GP04: J1.6, J2.8, pico1.6 (GP4)
/GP08: J1.11, J2.4, pico1.11 (GP8)
/GP09: J1.12, J2.6, pico1.12 (GP9)
/GP10: J1.14, R2.1, pico1.14 (GP10)
/GP11: J1.15, Rb_150.2, pico1.15 (GP11)
/GP12: J1.16, Rr_220.2, pico1.16 (GP12)
/GP13: J1.17, Rg_220.2, pico1.17 (GP13)
/GP16: J2.11, J3.1, pico1.21 (GP16)
/GP17: J2.9, J3.2, pico1.22 (GP17)
/GP18: J2.14, J3.4, pico1.24 (GP18)
/GP19: J2.12, J3.5, pico1.25 (GP19)
/GP20: J2.10, J3.6, pico1.26 (GP20)
/GP28: J2.5, J3.14, J4.2, J5.4, pico1.34 (GP28)
/GP28_EXT: J6.2, J8.1, J8.2
/in: J1.10, J14.2, J22.3, pico1.10 (GP7)
/pino_07: J1.7, SW2.1, pico1.7 (GP5)
/pino_09: J1.9, SW3.1, pico1.9 (GP6)
/pino_19: J1.19, OLED1.4 (SDA), pico1.19 (GP14)
/pino_20: J1.20, OLED1.3 (SCL), pico1.20 (GP15)
/pino_27: J3.7, R1.1, pico1.27 (GP21)
/pino_29: J3.9, J19.5, pico1.29 (GP22); also elsewhere on the board
/pino_30: J3.10, SW1.1, pico1.30 (RUN)
/pino_31: J3.11, J19.3, pico1.31 (GP26); also elsewhere on the board
/pino_32: J3.12, J19.4, pico1.32 (GP27); also elsewhere on the board
/pino_37: J3.17, pico1.37 (3V3_EN)
GNDREF: BT1.2 (-), C1.2, C2.2, C3.2, C4.2, CARGA_SOLAR1.1, Charge_DisCharge1.2 (GND), Charge_DisCharge1.4 (GND), Charge_DisCharge1.5 (GND), D1.1 (RK), D1.2 (GK), D1.3 (BK), D2.2 (K), D3.2 (A), J1.3, J1.8, J1.13, J1.18, J2.1, J2.7, J2.13, J3.3, J3.8, J3.13, J3.18, J5.3, J5.5, J12.5, J14.1, J14.4, J19.1, J20.4, J21.4, J22.1, J22.4, OLED1.1 (GND), Q2.3 (E), Q3.3 (E), R_pulldown1.2, Reg_3V3.1 (ADJ), SW1.2, SW2.2, SW3.2, U1.1, U4.2 (GND), V_BAT1.1, pico1.3 (GND), pico1.8 (GND), pico1.13 (GND), pico1.18 (GND), pico1.23 (GND), pico1.28 (GND), pico1.33 (AGND), pico1.38 (GND); also elsewhere on the board
unnamed: BZ1.2 (+), BZ2.2 (+), Q2.1 (C)
unnamed: BZ3.2 (+), BZ4.2 (+), Q3.1 (C)
unnamed: CARGA_SOLAR1.2, R_1W1.2
unnamed: Charge_DisCharge1.1 (OUT5V), Q1.3 (D)
unnamed: D1.4 (BA), D2.3 (BA), Rb_150.1
unnamed: D1.5 (GA), D2.4 (GA), Rg_220.1
unnamed: D1.6 (RA), D2.1 (RA), Rr_220.1
unnamed: D3.1 (K), D4.2 (A), R_1W1.1
unnamed: J4.1, U4.1 (OUT)
unnamed: Q2.2 (B), R1.2
unnamed: Q3.2 (B), R2.2
VBUS: Charge_DisCharge1.6 (VIN), D4.1 (K), J3.20, Q1.1 (G), R_pulldown1.1, pico1.40 (VBUS)
VSYS: BZ1.1 (-), BZ2.1 (-), BZ3.1 (-), BZ4.1 (-), C1.1, C3.1, J2.2, J3.19, J5.1, J14.3, J22.2, Q1.2 (S), Reg_3V3.3 (VI), U1.3, pico1.39 (VSYS)
VSYS_EXT: J6.5, J11.1, J11.2
V_BAT +: BT1.1 (+), Charge_DisCharge1.3 (BAT), V_BAT1.2

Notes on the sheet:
POWER
OLED
BUZZERS
LEDS RGB
BUTTONS
MICROPHONE
CONNECTOR_IDC
CONNECTOR JACARÉ
CHARGE
MATRIX OF LEDS
RASPBERRY_PI_PICO_W
JOYSTICK
